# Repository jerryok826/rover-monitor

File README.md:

# Rover Monitor
Rover monitor is a simple info display for the JPL's open-source-rover project
# My initial Rover Testing

# Rover info monitor.
### Rover ROS2 Off

### Rover ROS2 Running

### Voltage fault: Below 12.0 V

## Rover Monitor Project Description
I wanted a convenient way to start/stop, shutdown and monitor the rover for problems. The board just uses the RPI's GPIO to drive the board with some C code. The code boots from startup and monitors the rover's battery voltage and current. It’s also convenient to have the rover's hostname for remote login. The V and I readings come from the rover's on board ina260 via i2c. Been using the board for login info and shutdown for about a month.

Monitor Features:
1. Local login info.
2. Rover shutdown button.
3. Rover ROS run and stop button.
4. Voltage and current monitoring with audio alarm on fault.
5. Monitor beeps when system has complteted booting and ready for operation.

### Project Status
Basically complete, except for a fault event detail line to the display. Below is the original prototype version.

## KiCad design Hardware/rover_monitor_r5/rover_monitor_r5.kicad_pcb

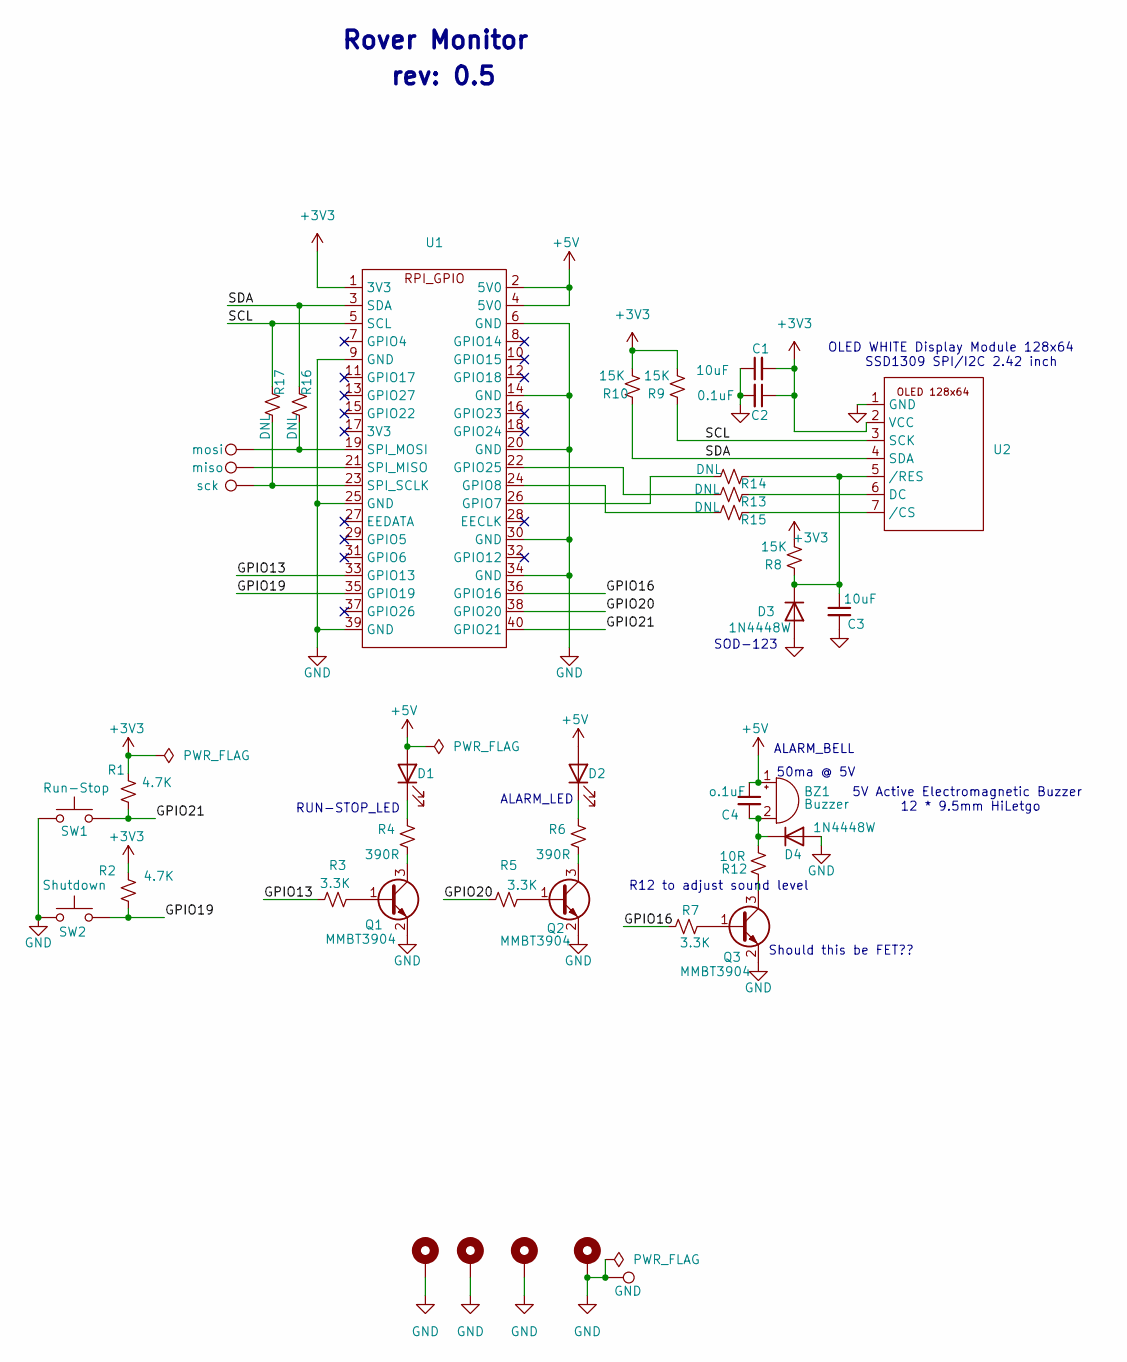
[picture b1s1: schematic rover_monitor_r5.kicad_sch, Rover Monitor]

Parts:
BZ1: Buzzer; Buzzer_12x9.5RM7.6
C1, C3: 10uF; C_0805_2012Metric_Pad1.18x1.45mm_HandSolder
C2: 0.1uF; C_0805_2012Metric_Pad1.18x1.45mm_HandSolder
C4: o.1uF; C_0805_2012Metric_Pad1.18x1.45mm_HandSolder
D1: Run-Stop; LED_1206_3216Metric_Pad1.42x1.75mm_HandSolder
D2: Alarm; LED_1206_3216Metric_Pad1.42x1.75mm_HandSolder
D3, D4: 1N4448W; D_SOD-123
GND1: GND; TestPoint_THTPad_D2.0mm_Drill1.0mm
H1, H2, H3, H4: MountingHole_Pad; MountingHole_3.2mm_M3_ISO7380_Pad_TopBottom
Q1, Q2, Q3: MMBT3904; SOT-23
R1, R2: 4.7K; R_0805_2012Metric_Pad1.20x1.40mm_HandSolder
R3, R5, R7: 3.3K; R_0805_2012Metric_Pad1.20x1.40mm_HandSolder
R4, R6: 390R; R_0805_2012Metric_Pad1.20x1.40mm_HandSolder
R8, R9, R10: 15K; R_0805_2012Metric_Pad1.20x1.40mm_HandSolder
R12: 10R; R_0805_2012Metric_Pad1.20x1.40mm_HandSolder
R13, R14, R15, R16, R17: DNL; R_0805_2012Metric_Pad1.20x1.40mm_HandSolder
SW1: Run-Stop; SW_TH_Tactile_Omron_B3F-10xx
SW2: Shutdown; SW_TH_Tactile_Omron_B3F-10xx
U1: PinHeader_2x20_P2.54mm_Vertical
U2: oled_128x64_r2
miso1: miso; TestPoint_THTPad_D2.0mm_Drill1.0mm
mosi1: mosi; TestPoint_THTPad_D2.0mm_Drill1.0mm
sck1: sck; TestPoint_THTPad_D2.0mm_Drill1.0mm

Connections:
+3V3: C1.2, C2.1, R1.1, R2.1, R8.1, R9.1, R10.1, U1.1 (3V3), U2.2 (VCC)
+5V: BZ1.1 (+), C4.1, D1.2 (A), D2.2 (A), U1.2 (5V0), U1.4 (5V0)
/GPIO13: R3.2, U1.33 (GPIO13)
/GPIO16: R7.2, U1.36 (GPIO16)
/GPIO19: R2.2, SW2.2, U1.35 (GPIO19)
/GPIO20: R5.2, U1.38 (GPIO20)
/GPIO21: R1.2, SW1.2, U1.40 (GPIO21)
/SCL: R9.2, R17.2, U1.5 (SCL), U2.3 (SCK)
/SDA: R10.2, R16.2, U1.3 (SDA), U2.4 (SDA)
GND: C1.1, C2.2, C3.2, D3.2 (A), D4.2 (A), GND1.1, H1.1, H2.1, H3.1, H4.1, Q1.2 (E), Q2.2 (E), Q3.2 (E), SW1.1, SW2.1, U1.6 (GND), U1.9 (GND), U1.14 (GND), U1.20 (GND), U1.25 (GND), U1.30 (GND), U1.34 (GND), U1.39 (GND), U2.1 (GND)
unnamed: BZ1.2 (-), C4.2, D4.1 (K), R12.1
unnamed: D1.1 (K), R4.1
unnamed: D2.1 (K), R6.1
unnamed: C3.1, D3.1 (K), R8.2, R14.2, U2.5 (/RES)
unnamed: Q1.1 (B), R3.1
unnamed: Q1.3 (C), R4.2
unnamed: Q2.1 (B), R5.1
unnamed: Q2.3 (C), R6.2
unnamed: Q3.1 (B), R7.1
unnamed: Q3.3 (C), R12.2
unnamed: R14.1, U1.26 (GPIO7)
unnamed: R15.1, U1.24 (GPIO8)
unnamed: R13.1, U1.22 (GPIO25)
unnamed: U1.21 (SPI_MISO), miso1.1
unnamed: R16.1, U1.19 (SPI_MOSI), mosi1.1
unnamed: R17.1, U1.23 (SPI_SCLK), sck1.1
unnamed: R13.2, U2.6 (DC)
unnamed: R15.2, U2.7 (/CS)

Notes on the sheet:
RUN-STOP_LED
ALARM_BELL
rev: 0.5
SOD-123
Rover Monitor
50ma @ 5V
Should this be FET??
OLED WHITE Display Module 128x64 SSD1309 SPI/I2C 2.42 inch
ALARM_LED
5V Active Electromagnetic Buzzer 12 * 9.5mm HiLetgo
R12 to adjust sound level

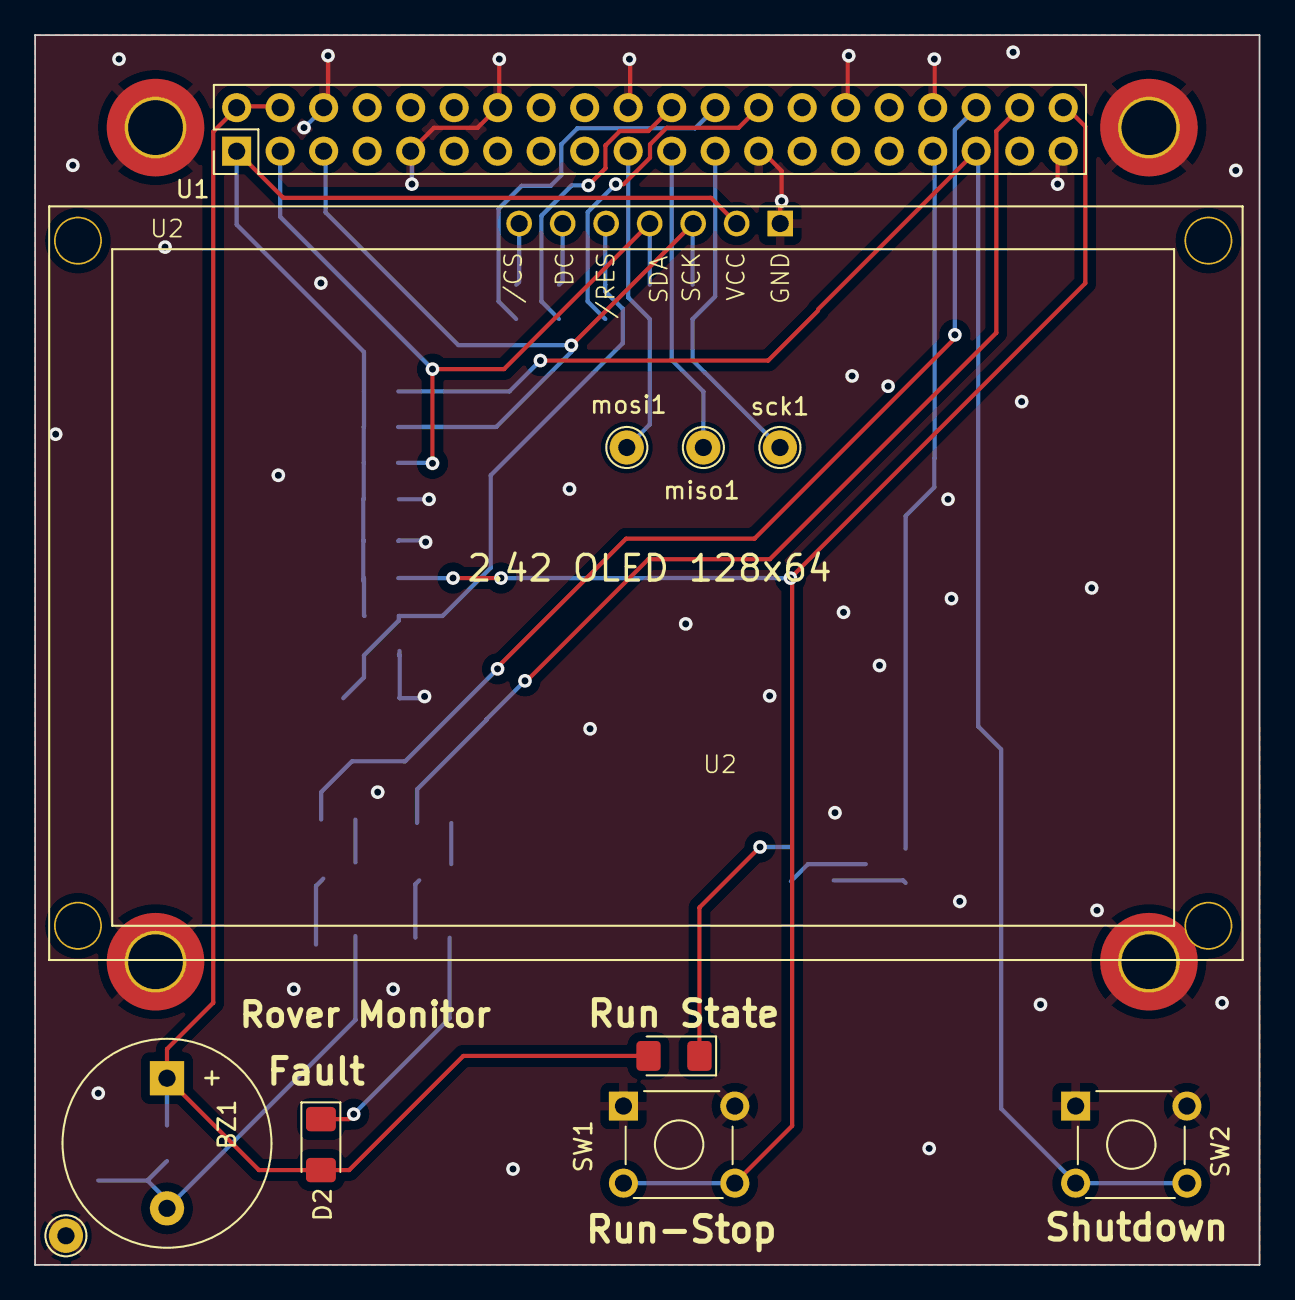
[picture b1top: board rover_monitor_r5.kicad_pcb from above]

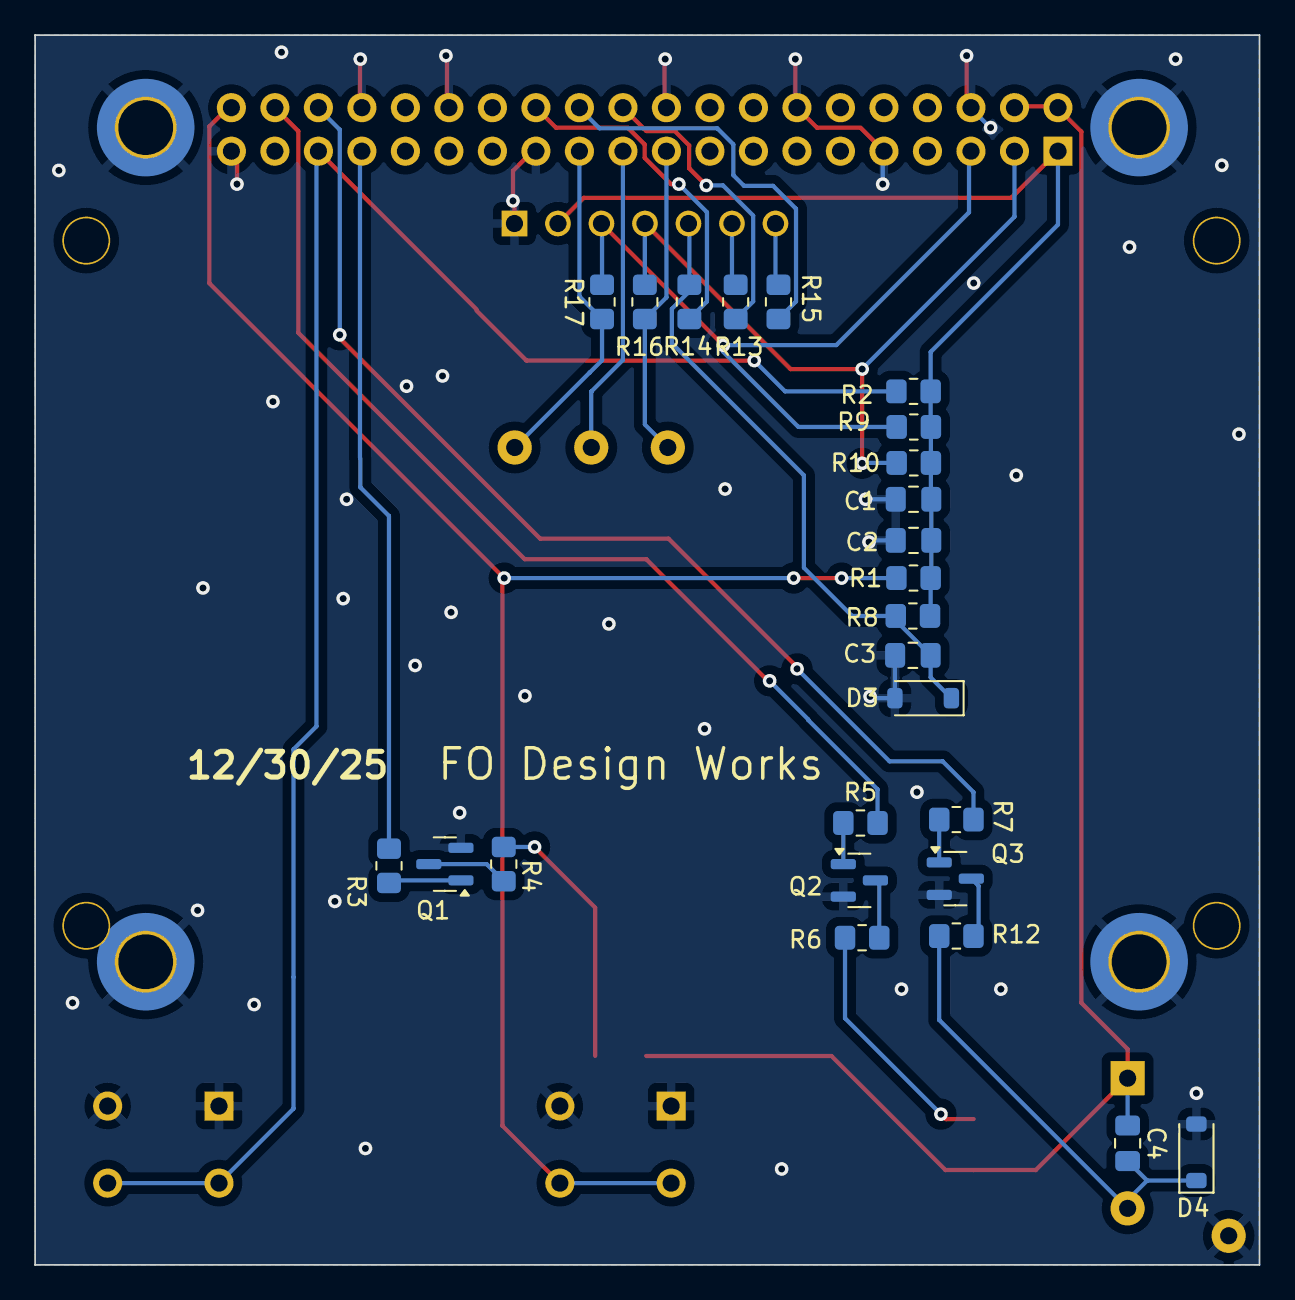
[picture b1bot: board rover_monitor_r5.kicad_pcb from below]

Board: 2 copper layers, 71.5 x 71.8 mm, 41 parts (25 on the bottom side), 28 nets.

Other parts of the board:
U2#2: oled_128x64_r2

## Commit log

2025-11-21 update sch
2025-11-21 rename gerber file
2025-12-11 update power readout support
2025-12-11 code clean up
2025-12-11 updated photos
2025-12-19 correct rover stop support
2025-12-19 add user notes
2025-12-20 update images
2025-12-31 better button support
2025-12-31 breakout ssd1306 driver
2026-01-01 add gpio output driver
